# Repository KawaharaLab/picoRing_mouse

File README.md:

# picoRing_mouse
pip install -r GUI/requirements.txt

python3 GUI/main.py -i GUI/setting/default.ini

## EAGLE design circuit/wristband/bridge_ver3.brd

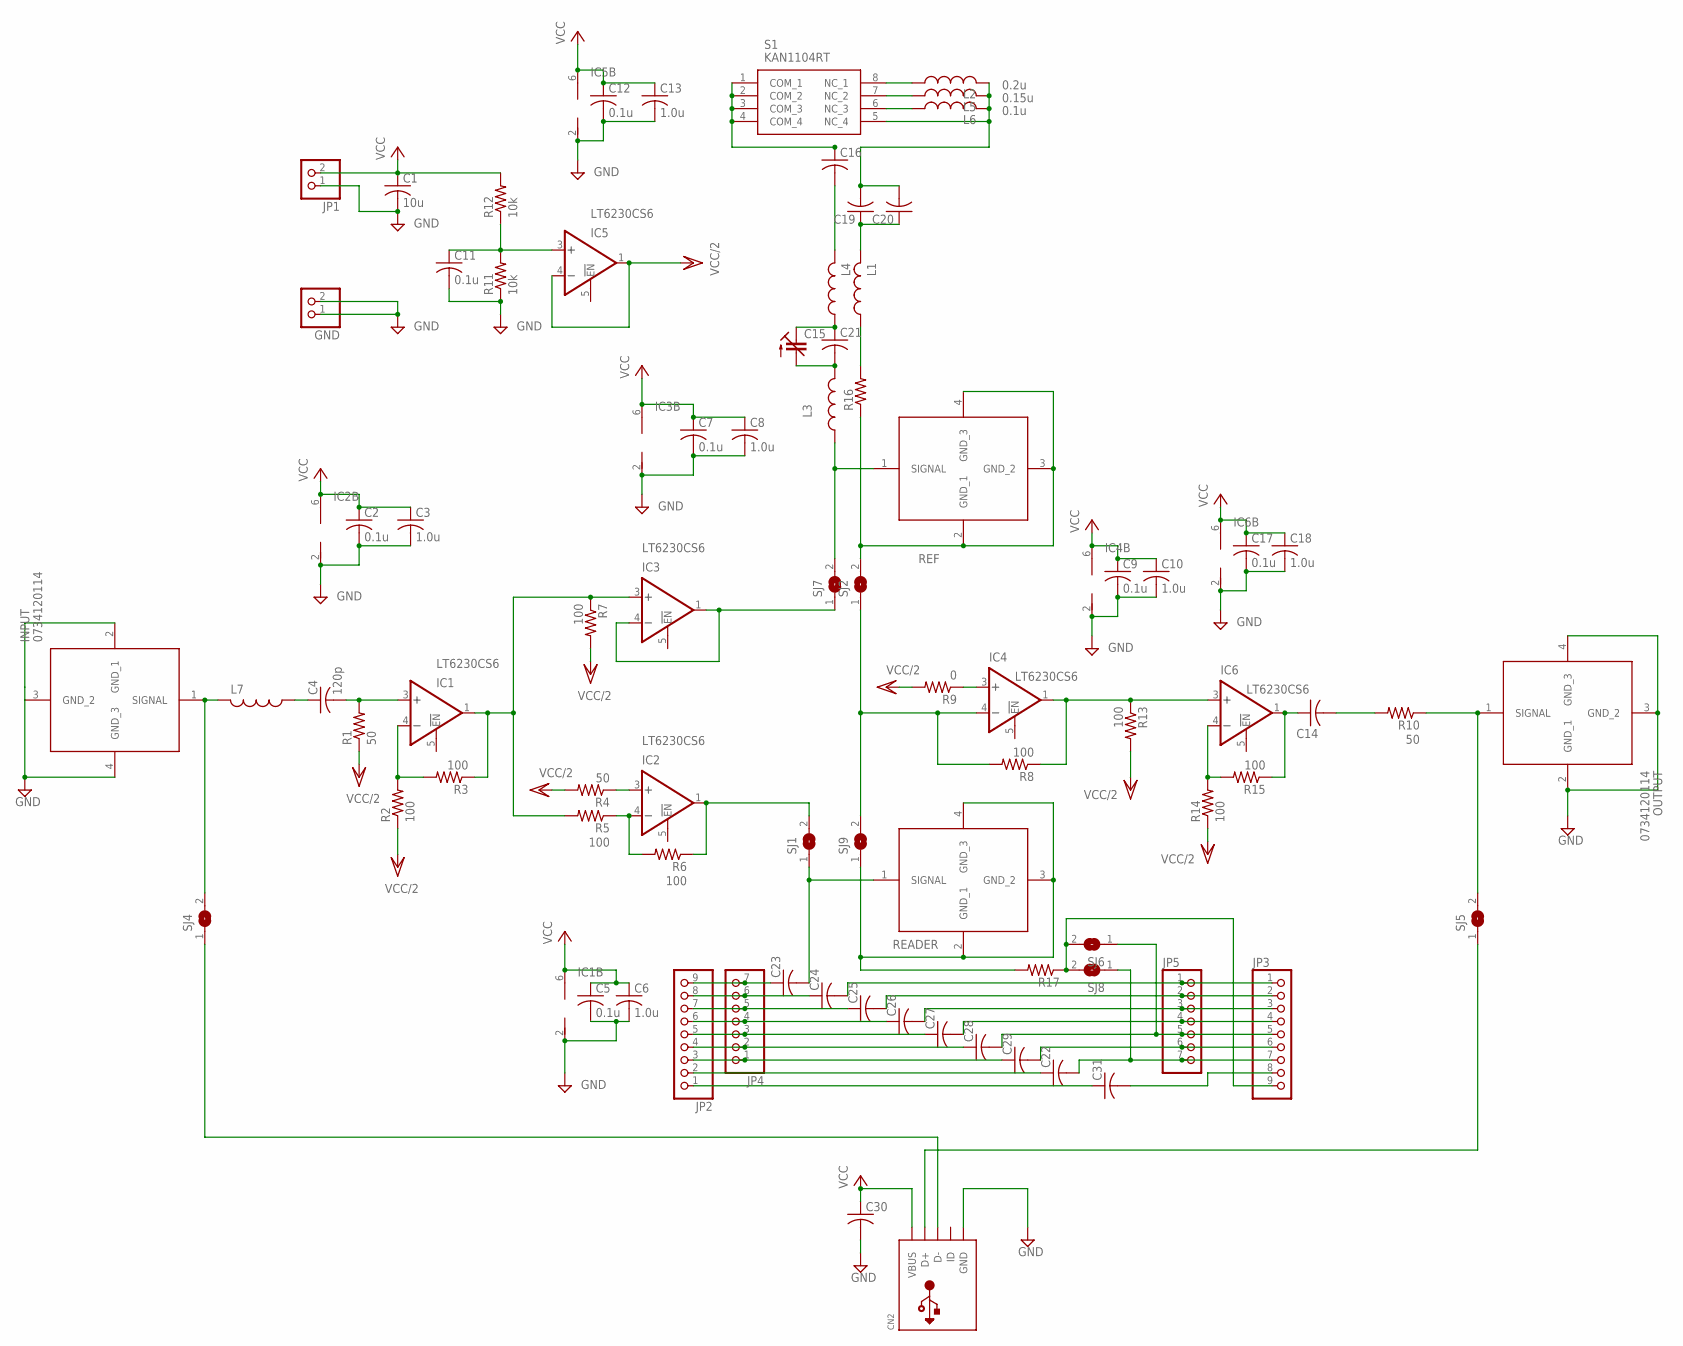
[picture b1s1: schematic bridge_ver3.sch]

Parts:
C1: 10u; C0603K
C2, C5, C7, C9, C11, C12, C17: 0.1u; C0603K
C3, C6, C8, C10, C13, C18: 1.0u; C0603K
C4: 120p; C0603K
C14: C-USC0603K; C0603K
C15: C-TRIMMTZBX4; CTRIMTZBX4
C16, C19, C20, C21, C22, C23, C24, C25, C26, C27, C28, C29, C30, C31: C-USC1608; C1608
CN2: USBMICRO_20329; 4UCONN_20329
GND: PINHD-1X2; 1X02
IC1, IC2, IC3, IC4, IC5, IC6: LT6230CS6; TSOT23-6
INPUT: 0734120114
JP1: PINHD-1X2; 1X02
JP2, JP3: PINHD-1X9; 1X09
JP4, JP5: PINHD-1X7; 1X07
L1, L3, L4, L7: L-USL2012C; L2012C
L2: 0.2u; L2012C
L5: 0.15u; L2012C
L6: 0.1u; L2012C
OUTPUT: 0734120114
R1, R4, R10: 50; R0603
R2, R3, R5, R6, R7, R8, R13, R14, R15: 100; R0603
R9: 0; R0603
R11, R12: 10k; R0603
R16, R17: R-US_R0603; R0603
READER: 0734120114
REF: 0734120114
S1: KAN1104RT
SJ1, SJ2, SJ4, SJ5, SJ6, SJ7, SJ8, SJ9: SJ

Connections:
GND: C1.2, C2.2, C3.2, C5.2, C6.2, C7.2, C8.2, C9.2, C10.2, C11.2, C12.2, C13.2, C17.2, C18.2, C30.2, CN2.BASE@1 (GND), CN2.BASE@2 (GND), CN2.GND, CN2.SPRT@1 (GND), CN2.SPRT@2 (GND), CN2.SPRT@3 (GND), CN2.SPRT@4 (GND), GND.1, GND.2, IC1.2 (V-), IC2.2 (V-), IC3.2 (V-), IC4.2 (V-), IC5.2 (V-), IC6.2 (V-), INPUT.2 (GND_1), INPUT.3 (GND_2), INPUT.4 (GND_3), JP1.1, OUTPUT.2 (GND_1), OUTPUT.3 (GND_2), OUTPUT.4 (GND_3), R11.1
unnamed: IC2.1 (OUT), R6.1, SJ1.2
unnamed: C4.2, IC1.3 (+IN), R1.2
unnamed: C22.1, JP2.2
unnamed: IC2.3 (+IN), R4.1
unnamed: C14.2, R10.2
unnamed: IC4.3 (+IN), R9.1
unnamed: IC1.1 (OUT), IC3.3 (+IN), R3.1, R5.2, R7.1
unnamed: L3.1, REF.1 (SIGNAL), SJ7.2
unnamed: C16.2, L4.2
unnamed: C23.1, JP2.9, JP4.7
unnamed: IC2.4 (-IN), R5.1, R6.2
unnamed: IC1.4 (-IN), R2.2, R3.2
unnamed: INPUT.1 (SIGNAL), L7.2, SJ4.2
unnamed: C11.1, IC5.3 (+IN), R11.2, R12.1
unnamed: IC4.4 (-IN), R8.2, SJ2.1, SJ9.2
unnamed: C14.1, IC6.1 (OUT), R15.1
unnamed: IC4.1 (OUT), IC6.3 (+IN), R8.1, R13.1
unnamed: IC6.4 (-IN), R14.2, R15.2
unnamed: IC3.1 (OUT), IC3.4 (-IN), SJ7.1
unnamed: CN2.D+, SJ5.1
unnamed: C15.2 (A), C21.2, L3.2
unnamed: C15.1 (E), C21.1, L4.1
unnamed: C16.1, S1.1 (COM_1), S1.2 (COM_2), S1.3 (COM_3), S1.4 (COM_4)
unnamed: L1.1, R16.2
unnamed: OUTPUT.1 (SIGNAL), R10.1, SJ5.2
unnamed: C24.2, JP3.1, JP5.1
unnamed: C24.1, JP2.8, JP4.6
unnamed: C25.2, JP3.2, JP5.2
unnamed: C25.1, JP2.7, JP4.5
unnamed: C26.2, JP3.3, JP5.3
unnamed: C26.1, JP2.6, JP4.4
unnamed: C27.2, JP3.4, JP5.4
unnamed: C27.1, JP2.5, JP4.3
unnamed: C28.1, JP2.4, JP4.2
unnamed: C28.2, JP3.5, JP5.5, SJ6.1
unnamed: C29.2, JP3.6, JP5.6
unnamed: C29.1, JP2.3, JP4.1
unnamed: R16.1, REF.2 (GND_1), REF.3 (GND_2), REF.4 (GND_3), SJ2.2
unnamed: C4.1, L7.1
unnamed: CN2.D-, SJ4.1
unnamed: C23.2, READER.1 (SIGNAL), SJ1.1
unnamed: JP3.9, R17.1, SJ6.2, SJ8.2
unnamed: C31.2, JP3.8
unnamed: C31.1, JP2.1
unnamed: C22.2, JP3.7, JP5.7, SJ8.1
unnamed: R17.2, READER.2 (GND_1), READER.3 (GND_2), READER.4 (GND_3), SJ9.1
unnamed: L2.1, S1.8 (NC_1)
unnamed: L5.1, S1.7 (NC_2)
unnamed: L6.1, S1.6 (NC_3)
unnamed: C19.2, C20.2, L2.2, L5.2, L6.2, S1.5 (NC_4)
unnamed: C19.1, C20.1, L1.2
VCC: C1.1, C2.1, C3.1, C5.1, C6.1, C7.1, C8.1, C9.1, C10.1, C12.1, C13.1, C17.1, C18.1, C30.1, CN2.VBUS, IC1.6 (V+), IC2.6 (V+), IC3.6 (V+), IC4.6 (V+), IC5.6 (V+), IC6.6 (V+), JP1.2, R12.2
VCC/2: IC5.1 (OUT), IC5.4 (-IN), R1.1, R2.1, R4.2, R7.2, R9.2, R13.2, R14.1

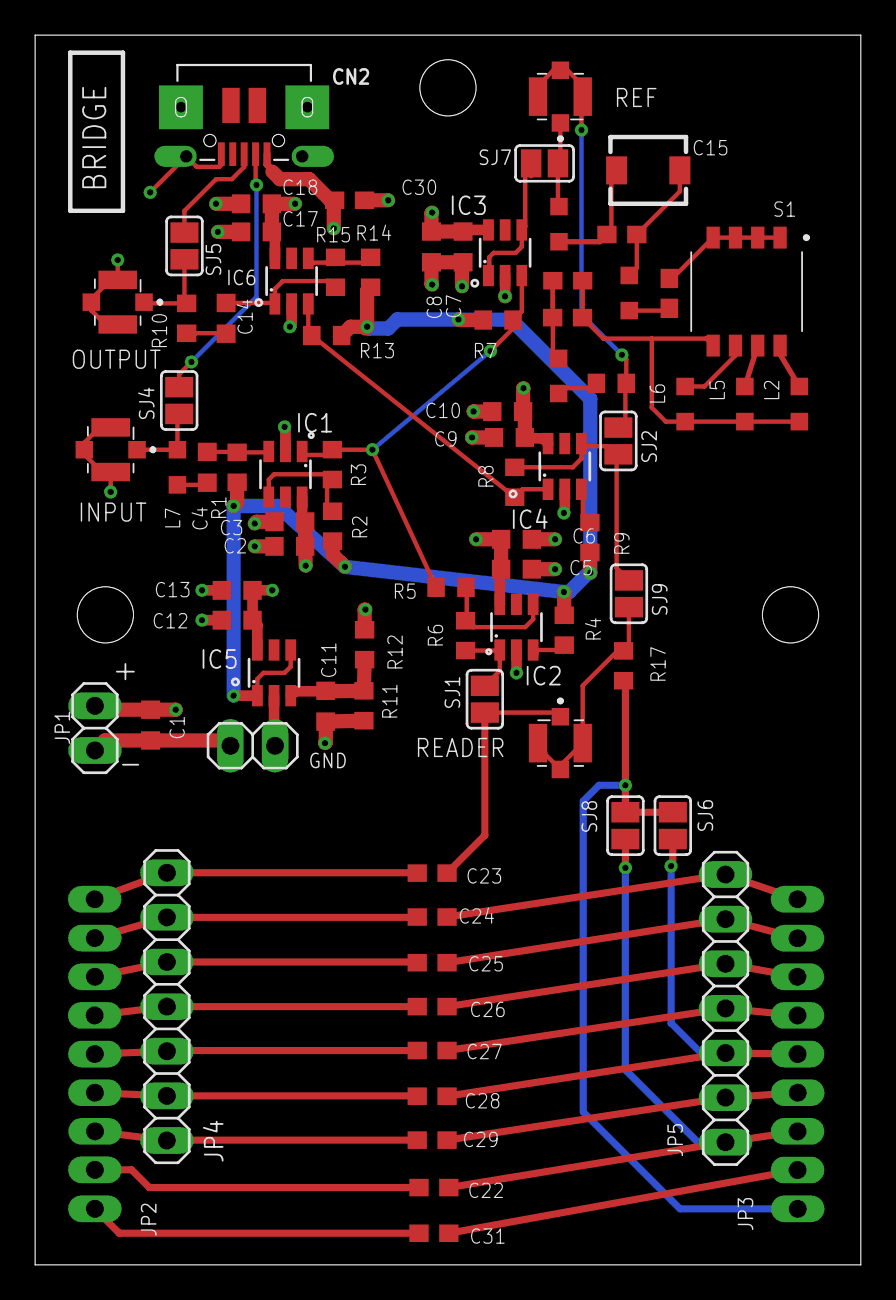
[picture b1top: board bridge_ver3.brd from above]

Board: 4 copper layers, 47.0 x 70.0 mm, 81 parts (0 on the bottom side), 54 nets.

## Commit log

2025-06-24 init
2025-06-24 GUI_delete
2025-06-25 rename wristband
2025-06-25 add wristband
2025-06-25 Add .DS_Store to .gitignore
2025-11-21 switch to yamamoto
2025-11-21 Add installation and execution instructions
2025-11-21 Add instruction to run main.py with default settings

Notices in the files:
parts and their libraries:
microbuilder: This work is placed in the public domain, and may be freely used for commercial and non-commercial work with the following conditions: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
